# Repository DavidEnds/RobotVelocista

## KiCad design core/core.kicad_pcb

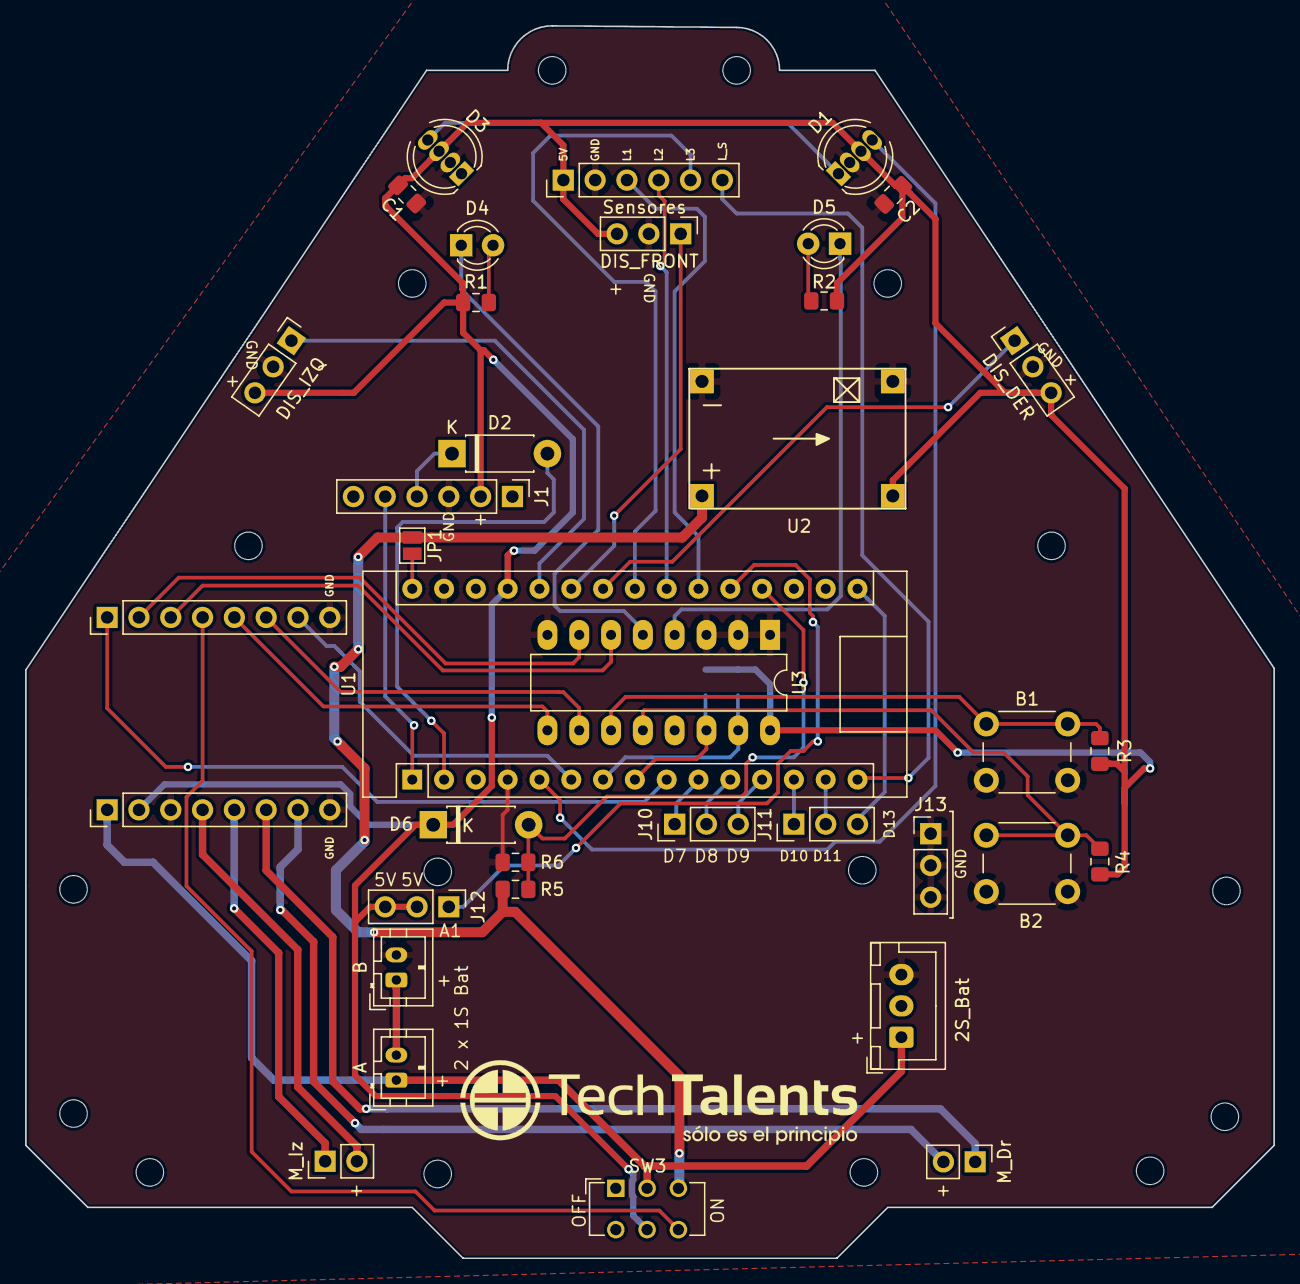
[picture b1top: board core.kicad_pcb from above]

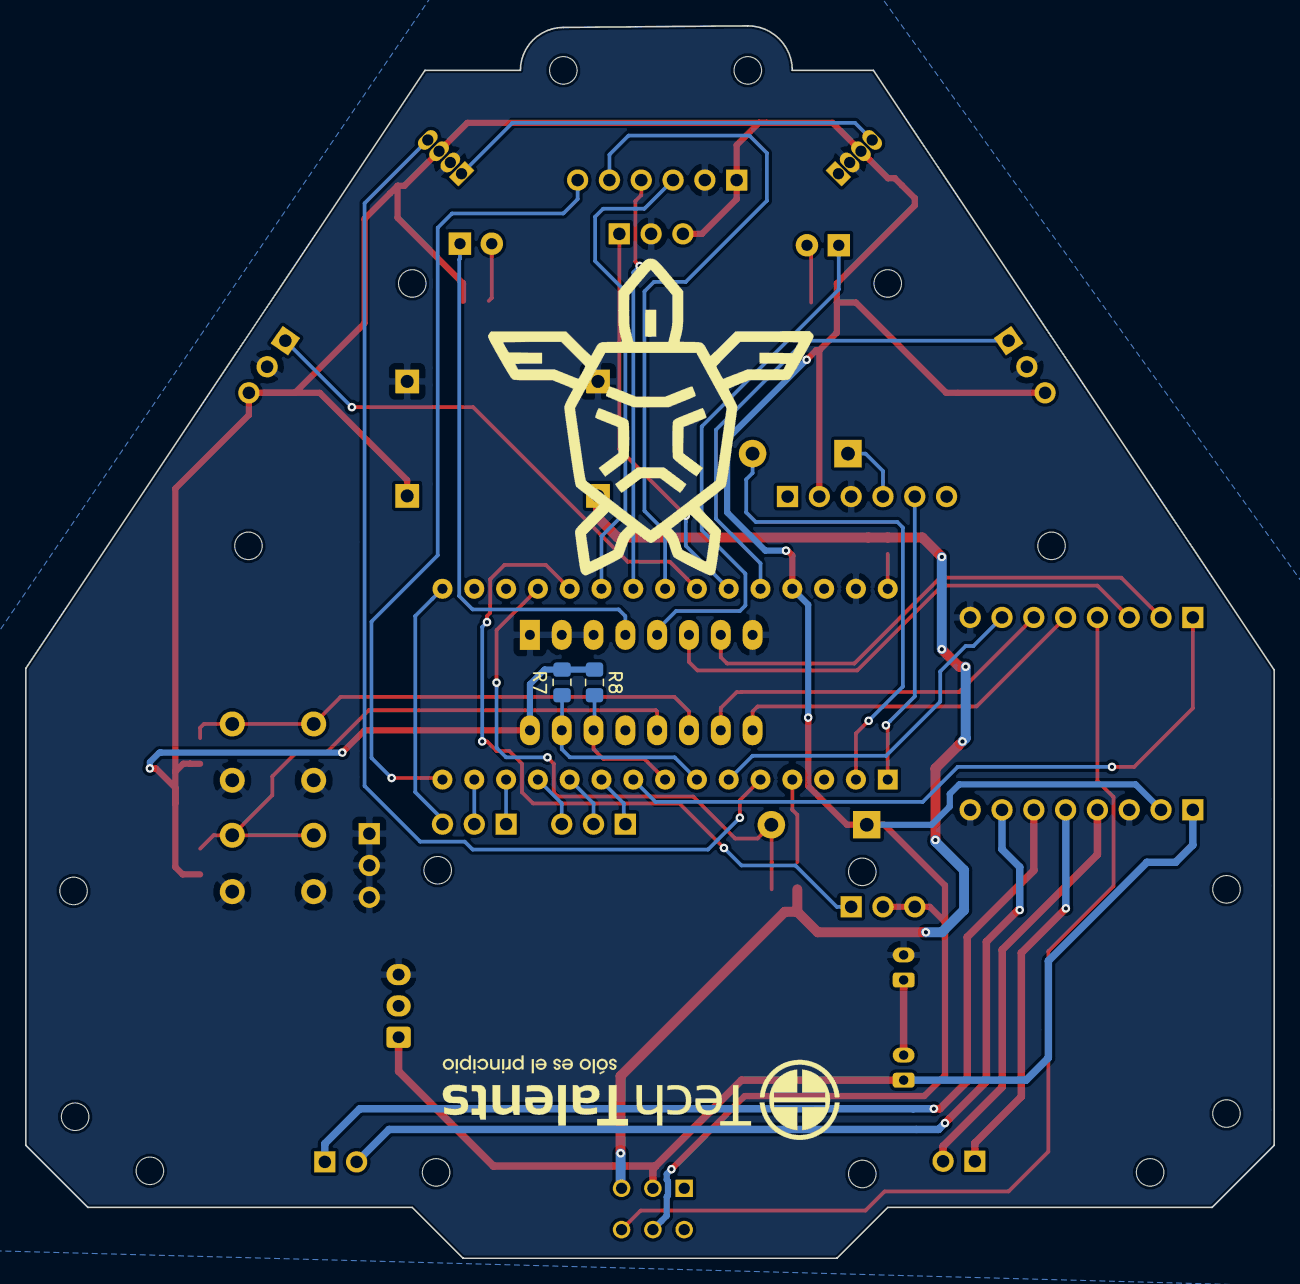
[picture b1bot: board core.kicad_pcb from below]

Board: 2 copper layers, 99.7 x 98.4 mm, 39 parts (2 on the bottom side), 45 nets.

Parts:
2S_Bat: LIPO_2S; JST_XH_B03B-XH-A_1x03_P2.50mm_Vertical
A: LIPO_1S_A; JST_PH_B2B-PH-K_1x02_P2.00mm_Vertical
B: LIPO_1S_B; JST_PH_B2B-PH-K_1x02_P2.00mm_Vertical
B1: B1; SW_PUSH_6mm
B2: B2; SW_PUSH_6mm
C1, C2: 100nF; C_0805_2012Metric_Pad1.15x1.40mm_HandSolder
D1: NEO1; LED_D5.0mm-4_RGB
D2: 1N4148; D_DO-41_SOD81_P7.62mm_Horizontal
D3: NEO2; LED_D5.0mm-4_RGB
D4: ROJO; LED_D3.0mm
D5: VERDE; LED_D3.0mm
D6: 1N4001; D_DO-41_SOD81_P7.62mm_Horizontal
DIS_DER: DIST_DCHA; PinHeader_1x03_P2.54mm_Vertical
DIS_FRONT: DIST_FRONT; PinHeader_1x03_P2.54mm_Vertical
DIS_IZQ: DIST_IZQ; PinHeader_1x03_P2.54mm_Vertical
J1: HC-05; PinHeader_1x06_P2.54mm_Vertical
J2: TB6612FNG_A; PinHeader_1x08_P2.54mm_Vertical
J5: TB6612FNG_B; PinHeader_1x08_P2.54mm_Vertical
J10: AUX1; PinHeader_1x03_P2.54mm_Vertical
J11: AUX2; PinHeader_1x03_P2.54mm_Vertical
J12: AUX3; PinHeader_1x03_P2.54mm_Vertical
J13: AUX4; PinHeader_1x03_P2.54mm_Vertical
JP1: Jumper; SolderJumper-2_P1.3mm_Open_Pad1.0x1.5mm
M_Dr: MOT_DER; PinHeader_1x02_P2.54mm_Vertical
M_Iz: MOT_IZQ; PinHeader_1x02_P2.54mm_Vertical
R1, R2: 220; R_0805_2012Metric_Pad1.15x1.40mm_HandSolder
R3, R4: 10K; R_0805_2012Metric_Pad1.15x1.40mm_HandSolder
R5: 82K; R_0805_2012Metric_Pad1.15x1.40mm_HandSolder
R6: 120K; R_0805_2012Metric_Pad1.15x1.40mm_HandSolder
R7, R8: 1k; R_0805_2012Metric_Pad1.15x1.40mm_HandSolder
SW3: SW_DPDT_x2; SW_CuK_JS202011CQN_DPDT_Straight
Sensores: Sensores_linea; PinHeader_1x06_P2.54mm_Vertical
U1: Arduino_Nano_v3.x; Arduino_Nano
U2: DC-DC_BuckModule; DC-DC-MP2307
U3: PCF8574; DIP-16_W7.62mm_LongPads

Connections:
+5V: C1.2, C2.2, D1.3, D3.3, D6.1, DIS_DER.3, DIS_FRONT.3, DIS_IZQ.3, J1.2, J2.2, J12.2, J12.3, R1.1, R2.1, R3.1, R4.1, R7.1, R8.1, SW3.5, Sensores.1, U1.27, U2.3, U3.16
A1: J12.1, U1.20
B1: B1.1, R3.2, U3.11
B2: B2.1, R4.2, U3.12
BAT: D6.2, R5.2, R6.1, U1.19
BT_RX: J1.5, U1.1
BT_TX: D2.2, U1.2
D7: J10.1, U1.10
D8: J10.2, U1.11
D9: J10.3, U1.12
D10: J11.1, U1.13
D11: J11.2, U1.14
D13: J11.3, U1.16
DIR_DER_1: J5.5, U3.9
DIR_DER_2: J5.6, U3.10
DIR_IZQ_1: J5.3, U3.6
DIR_IZQ_2: J5.2, U3.7
DIST_DCHA: DIS_DER.1, U1.24
DIST_FRONT: DIS_FRONT.1, U1.25
DIST_IZQ: DIS_IZQ.1, U1.26
GND: 2S_Bat.3, B.2, B1.2, B2.2, C1.1, C2.1, D1.2, D3.2, DIS_DER.2, DIS_FRONT.2, DIS_IZQ.2, J1.3, J2.3, J2.8, J5.8, J13.1, J13.2, J13.3, R6.2, Sensores.2, U1.4, U1.29, U2.2, U2.4, U3.1, U3.2, U3.3, U3.8
I2C_SCL: R8.2, U1.8, U3.14
I2C_SDA: R7.2, U1.7, U3.15
LED_G: D5.1, U3.4
LED_R: D4.1, U3.5
LINEA_1: Sensores.3, U1.21
LINEA_2: Sensores.4, U1.22
LINEA_3: Sensores.5, U1.23
LINEA_SEL: Sensores.6, U1.15
M_DER_+: J2.7, M_Dr.2
M_DER_-: J2.6, M_Dr.1
M_IZQ_+: J2.4, M_Iz.2
M_IZQ_-: J2.5, M_Iz.1
NEO: D1.4, U1.5
unnamed: D1.1, D3.4
unnamed: D2.1, J1.4
unnamed: D4.2, R1.2
unnamed: D5.2, R2.2
unnamed: A.2, B.1
PWM_DER: J5.7, U1.6
PWM_IZQ: J5.1, U1.9
STBY_MOT: J5.4, SW3.6
VBAT: 2S_Bat.1, A.1, J2.1, SW3.2
VCC: JP1.2, U1.30
VDD: JP1.1, R5.1, SW3.3, U2.1

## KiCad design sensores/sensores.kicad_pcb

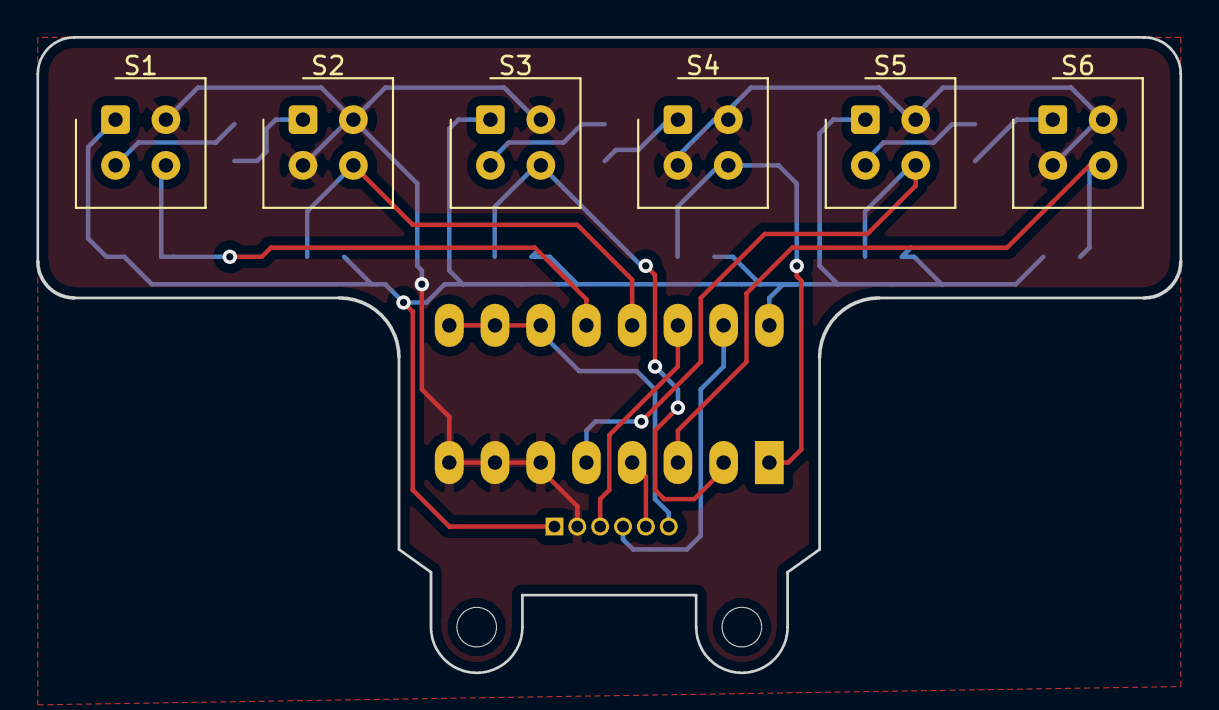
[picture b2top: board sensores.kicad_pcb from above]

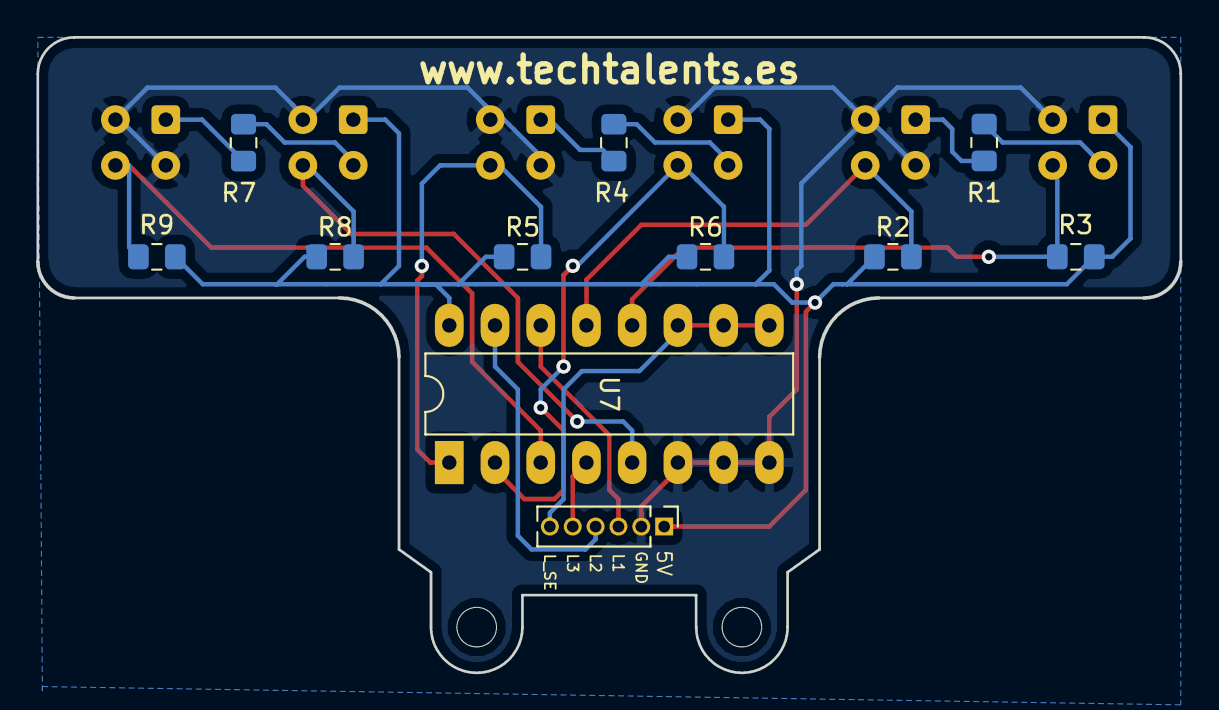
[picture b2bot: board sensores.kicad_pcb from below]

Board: 2 copper layers, 63.5 x 35.3 mm, 17 parts (11 on the bottom side), 18 nets.

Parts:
J1: Conn_01x06_Female; PinHeader_1x06_P1.27mm_Vertical
R1, R4, R7: 82; R_0805_2012Metric_Pad1.15x1.40mm_HandSolder
R2, R3, R5, R6, R8, R9: 10k; R_0805_2012Metric_Pad1.15x1.40mm_HandSolder
S1, S2, S3, S4, S5, S6: CNY70; Vishay_CNY70
U7: 4053; DIP-16_W7.62mm_LongPads

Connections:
+5V: J1.1, R2.1, R3.1, R5.1, R6.1, R8.1, R9.1, S1.1, S3.1, S5.1, U7.16
/linea1: J1.3, U7.14
/linea2: J1.4, U7.15
/linea3: J1.5, U7.4
/linea_selec: J1.6, U7.9, U7.10, U7.11
/sensor1: R3.2, S1.3, U7.12
/sensor2: R2.2, S2.3, U7.13
/sensor3: R6.2, S3.3, U7.2
/sensor4: R5.2, S4.3, U7.1
/sensor5: R8.2, S5.3, U7.5
/sensor6: R9.2, S6.3, U7.3
GND: J1.2, S1.4, S2.2, S2.4, S3.4, S4.2, S4.4, S5.4, S6.2, S6.4, U7.6, U7.7, U7.8
unnamed: R1.1, S1.2
unnamed: R1.2, S2.1
unnamed: R4.1, S3.2
unnamed: R4.2, S4.1
unnamed: R7.1, S5.2
unnamed: R7.2, S6.1

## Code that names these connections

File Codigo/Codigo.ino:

//EXPANSOR I2C PCF8574
#define SDA_PORT PORTD
#define SDA_PIN 4
#define SCL_PORT PORTD
#define SCL_PIN 5
#include <SoftWire.h>
SoftWire EXP = SoftWire();
const int expAddress = 0x20; //0x20 para PCF8574P; 0x38 para PCF8574AP
unsigned char expOutputRegister = 0b11111111;
void set_exp_value(char pin, char value);
byte get_exp_value(char pin);
#define EXP_P0    0
#define EXP_P1    1
#define EXP_P2    2
#define EXP_P3    3
#define EXP_P4    4
#define EXP_P5    5
#define EXP_P6    6
#define EXP_P7    7
#define VEL 255


// SENSORES DE LÍNEA
#define LINEA_1       A2
#define LINEA_2       A3
#define LINEA_3       A4
#define LINEA_SEL_1   12
#define LINEA_SEL_2   13
const int sensores_linea = 6;
unsigned int ADC_linea[sensores_linea];
void leer_sensores_linea(unsigned int* value);



// MOTORES
#define PWM_IZQ             6
#define PWM_DER             3
#define DIR_IZQ_1           EXP_P2
#define SET_DIR_IZQ_1_HIGH  set_exp_value(DIR_IZQ_1, HIGH)
#define SET_DIR_IZQ_1_LOW   set_exp_value(DIR_IZQ_1, LOW)
#define DIR_IZQ_2           EXP_P3
#define SET_DIR_IZQ_2_HIGH  set_exp_value(DIR_IZQ_2, HIGH)
#define SET_DIR_IZQ_2_LOW   set_exp_value(DIR_IZQ_2, LOW)
#define DIR_DER_1           EXP_P5
#define SET_DIR_DER_1_HIGH  set_exp_value(DIR_DER_1, HIGH)
#define SET_DIR_DER_1_LOW   set_exp_value(DIR_DER_1, LOW)
#define DIR_DER_2           EXP_P4
#define SET_DIR_DER_2_HIGH  set_exp_value(DIR_DER_2, HIGH)
#define SET_DIR_DER_2_LOW   set_exp_value(DIR_DER_2, LOW)




void setup() {
  pinMode(LINEA_SEL_1, OUTPUT);
  pinMode(LINEA_SEL_2, OUTPUT);
  pinMode(PWM_IZQ, OUTPUT);
  pinMode(PWM_DER, OUTPUT);

  Serial.begin(9600);
  EXP.begin();

}

void loop() {
  palante();
  /*
  leer_sensores_linea(ADC_linea);
  if(ADC_linea[2] >150 && ADC_linea[3] > 150){
      palante();
    
  }

  if(ADC_linea[2] > 150 && ADC_linea[3] < 150) {  //Negro el 2 y el 3 blanco
    derecha();
  }

  if(ADC_linea[3] > 150 && ADC_linea[2] < 150) {  //Negro el 2 y el 3 blanco
    izquierda();
  }

  if(ADC_linea[2] <150 && ADC_linea[3] < 150){
      parar();
    
  }
*/
  

/*
#ifdef TEST_MOTORES
  static int velocidad = 0;

  SET_DIR_IZQ_1_HIGH;
  SET_DIR_IZQ_2_LOW;
  SET_DIR_DER_1_HIGH;
  SET_DIR_DER_2_LOW;
  for(velocidad = 0; velocidad <= 255; velocidad += 1)
  {
    analogWrite(PWM_IZQ,velocidad);
    analogWrite(PWM_DER,velocidad);
    delay(10);
  }
  for(velocidad = 255; velocidad >= 0; velocidad -= 1)
  {
    analogWrite(PWM_IZQ,velocidad);
    analogWrite(PWM_DER,velocidad);
    delay(10);
  }

  SET_DIR_IZQ_1_LOW;
  SET_DIR_IZQ_2_HIGH;
  SET_DIR_DER_1_LOW;
  SET_DIR_DER_2_HIGH;
  for(velocidad = 0; velocidad >= -255; velocidad -= 1)
  {
    analogWrite(PWM_IZQ,-velocidad);
    analogWrite(PWM_DER,-velocidad);
    delay(10);
  }
  for(velocidad = -255; velocidad <= 0; velocidad += 1)
  {
    analogWrite(PWM_IZQ,-velocidad);
    analogWrite(PWM_DER,-velocidad);
    delay(10);
  }

  delay(1000);
#endif

*/

}

void set_exp_value(char pin, char value) {
  if(value == HIGH)
    expOutputRegister = expOutputRegister & (~(1<<pin));
  else // value == LOW
    expOutputRegister = expOutputRegister | (1<<pin);

  EXP.beginTransmission(expAddress);
  EXP.write(expOutputRegister);
  EXP.endTransmission();
}

byte get_exp_value(char pin) {
  byte value = 0;

  EXP.requestFrom(expAddress, 1);
  if(EXP.available())
    value = EXP.read();
  EXP.endTransmission();

  return (value & 1<<pin)>>pin;
}

void leer_sensores_linea(unsigned int* value) {
  digitalWrite(LINEA_SEL_1, LOW);
  value[0] = analogRead(LINEA_1);
  value[2] = analogRead(LINEA_2);
  value[4] = analogRead(LINEA_3);
  digitalWrite(LINEA_SEL_1, HIGH);
  value[1] = analogRead(LINEA_1);
  value[3] = analogRead(LINEA_2);
  value[5] = analogRead(LINEA_3);
}


void izquierda(){
  
    SET_DIR_IZQ_1_HIGH;
    SET_DIR_IZQ_2_LOW;
    SET_DIR_DER_1_LOW;
    SET_DIR_DER_2_HIGH;
    analogWrite(PWM_IZQ,VEL);
    analogWrite(PWM_DER,VEL);
}


void derecha(){
  
    SET_DIR_IZQ_1_LOW;
    SET_DIR_IZQ_2_HIGH;
    SET_DIR_DER_1_HIGH;
    SET_DIR_DER_2_LOW;
    analogWrite(PWM_IZQ,VEL);
    analogWrite(PWM_DER,VEL);
}


void palante(){
  
    SET_DIR_IZQ_1_LOW;
    SET_DIR_IZQ_2_HIGH;
    SET_DIR_DER_1_LOW;
    SET_DIR_DER_2_HIGH;
    analogWrite(PWM_IZQ,VEL);
    analogWrite(PWM_DER,VEL);
}



void parar(){
  
    SET_DIR_IZQ_1_LOW;
    SET_DIR_IZQ_2_HIGH;
    SET_DIR_DER_1_LOW;
    SET_DIR_DER_2_HIGH;
    analogWrite(PWM_IZQ,0);
    analogWrite(PWM_DER,0);
}

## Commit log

2018-11-27 Archivos subidos
2018-11-27 Gerbers exportados y mandado a fabrica
2018-12-01 Pdfs exportados
2019-03-02 Codigo subido
